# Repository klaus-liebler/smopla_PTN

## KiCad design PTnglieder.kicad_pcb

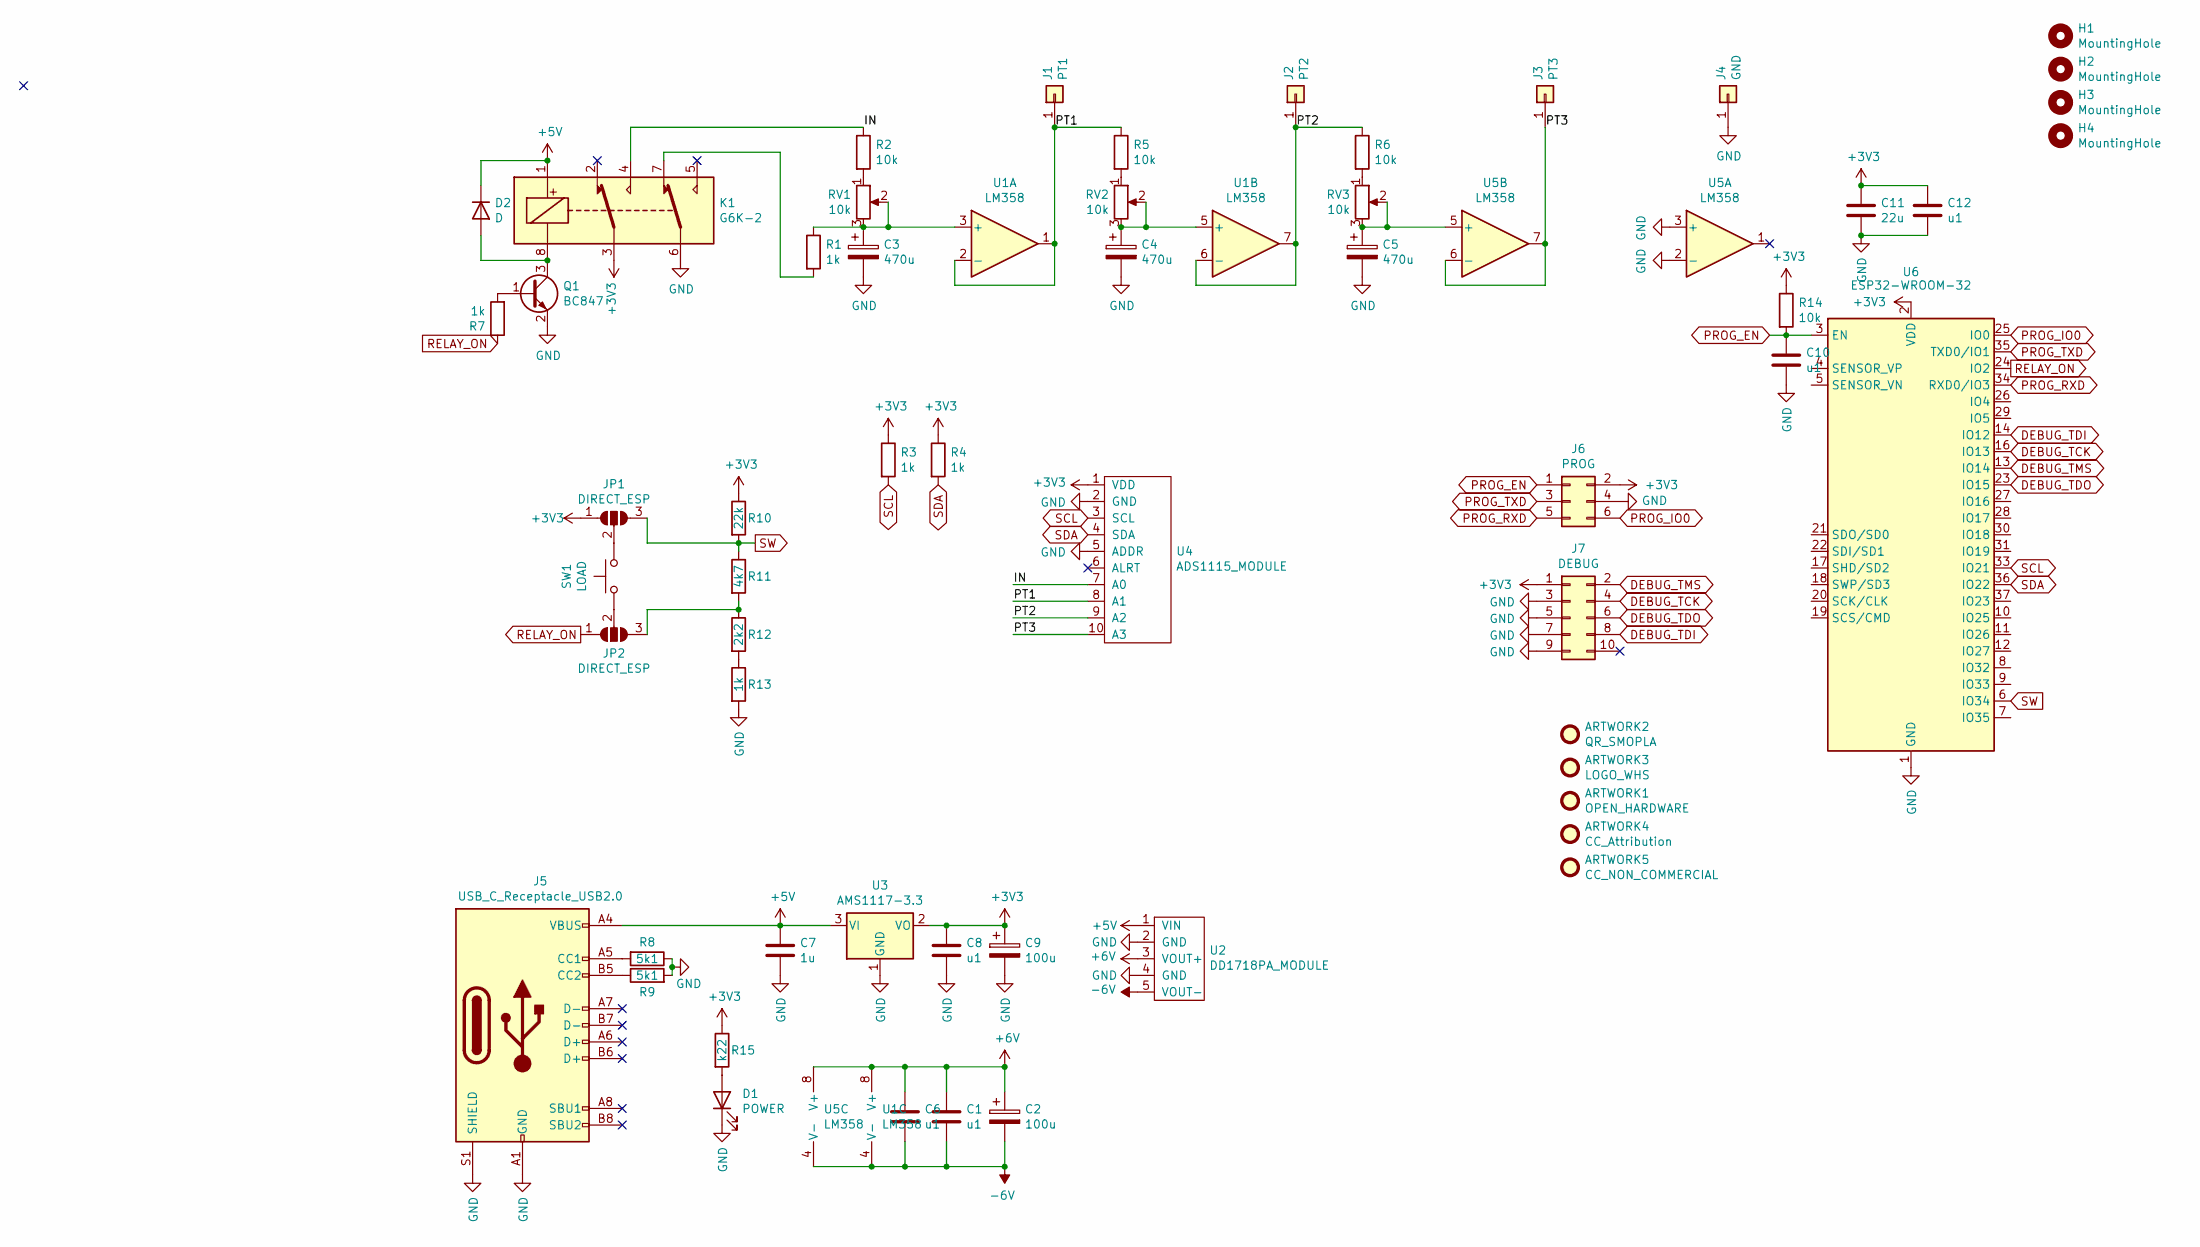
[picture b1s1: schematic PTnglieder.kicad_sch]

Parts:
ARTWORK1: OPEN_HARDWARE; OSHW-Logo2_14.6x12mm_Copper
ARTWORK2: QR_SMOPLA; QR_CODE_smopla_de
ARTWORK3: LOGO_WHS
ARTWORK4: CC_Attribution; Symbol_CC-Attribution_CopperTop_Big
ARTWORK5: CC_NON_COMMERCIAL; Symbol_CC-Noncommercial_CopperTop_Big
C1, C6, C8, C10, C12: u1; C_0805_2012Metric_Pad1.15x1.40mm_HandSolder
C2, C9: 100u; CP_Elec_6.3x5.7
C3, C4, C5: 470u; CP_Elec_10x10
C7: 1u; C_0805_2012Metric_Pad1.15x1.40mm_HandSolder
C11: 22u; C_1206_3216Metric_Pad1.42x1.75mm_HandSolder
D1: POWER; LED_D5.0mm
D2: D; D_SMA
H1, H2, H3, H4: MountingHole; MountingHole_3.2mm_M3_DIN965
J1: PT1; LABORATORY_JACK_RECESSED
J2: PT2; LABORATORY_JACK_RECESSED
J3: PT3; LABORATORY_JACK_RECESSED
J4: GND; LABORATORY_JACK_RECESSED
J5: USB_C_Receptacle_USB2.0; USB_C_Receptacle_HANDSOLDER
J6: PROG; PinHeader_2x03_P1.27mm_Vertical_SMD
J7: DEBUG; PinHeader_2x05_P1.27mm_Vertical_SMD
JP1, JP2: DIRECT_ESP; SolderJumper-3_P1.3mm_Open_RoundedPad1.0x1.5mm_NumberLabels
K1: G6K-2; Relay_DPDT_Omron_G6K-2F-Y_HANDSOLDER
Q1: BC847; SOT-23_Handsoldering
R1, R3, R4, R7, R13: 1k; R_0805_2012Metric_Pad1.15x1.40mm_HandSolder
R2, R5, R6, R14: 10k; R_0805_2012Metric_Pad1.15x1.40mm_HandSolder
R8, R9: 5k1; R_0805_2012Metric_Pad1.15x1.40mm_HandSolder
R10: 22k; R_0805_2012Metric_Pad1.15x1.40mm_HandSolder
R11: 4k7; R_0805_2012Metric_Pad1.15x1.40mm_HandSolder
R12: 2k2; R_0805_2012Metric_Pad1.15x1.40mm_HandSolder
R15: k22; R_0805_2012Metric_Pad1.15x1.40mm_HandSolder
RV1, RV2, RV3: 10k; Potentiometer_Alps_RK09K_Single_Vertical
SW1: LOAD; SW_PUSH-12mm_ANCHOR_CENTER
U1, U5: LM358; SOIC-8_3.9x4.9mm_Pitch1.27mm_handsolder
U2: DD1718PA_MODULE; DD1718PA_MODULE_SMD
U3: AMS1117-3.3; SOT-223-3_TabPin2_HANDSOLDER
U4: ADS1115_MODULE; ADS1115_MODULE_SMD
U6: ESP32-WROOM-32; ESP32-WROOM-32_HANDSOLDER

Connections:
+3V3: C8.1, C9.1, C11.1, C12.1, J6.2, J7.1, JP1.1 (A), K1.3, R3.1, R4.1, R10.1, R14.1, R15.1, U3.2 (VO), U4.1 (VDD), U6.2 (VDD)
+5V: C7.1, D2.1 (K), J5.A4 (VBUS), J5.A9 (VBUS), J5.B4 (VBUS), J5.B9 (VBUS), K1.1, U2.1 (VIN), U3.3 (VI)
+6V: C1.1, C2.1, C6.1, U1.8 (V+), U2.3 (VOUT+), U5.8 (V+)
-6V: C1.2, C2.2, C6.2, U1.4 (V-), U2.5 (VOUT-), U5.4 (V-)
/IN: K1.4, R2.1, U4.7 (A0)
/PT1: J1.1, R5.1, U1.1, U1.2 (-), U4.8 (A1)
/PT2: J2.1, R6.1, U1.6 (-), U1.7, U4.9 (A2)
/PT3: J3.1, U4.10 (A3), U5.6 (-), U5.7
DEBUG_TCK: J7.4, U6.16 (IO13)
DEBUG_TDI: J7.8, U6.14 (IO12)
DEBUG_TDO: J7.6, U6.23 (IO15)
DEBUG_TMS: J7.2, U6.13 (IO14)
GND: C3.2, C4.2, C5.2, C7.2, C8.2, C9.2, C10.2, C11.2, C12.2, D1.1 (K), J4.1, J5.A1 (GND), J5.A12 (GND), J5.B1 (GND), J5.B12 (GND), J5.S1 (SHIELD), J6.4, J7.3, J7.5, J7.7, J7.9, K1.6, Q1.2 (E), R8.1, R9.2, R13.2, U2.2 (GND), U2.4 (GND), U3.1 (GND), U4.2 (GND), U4.5 (ADDR), U5.2 (-), U5.3 (+), U6.1 (GND), U6.15 (GND), U6.38 (GND), U6.39 (GND)
unnamed: C3.1, R1.1, RV1.2, RV1.3, U1.3 (+)
unnamed: C4.1, RV2.2, RV2.3, U1.5 (+)
unnamed: C5.1, RV3.2, RV3.3, U5.5 (+)
unnamed: D1.2 (A), R15.2
unnamed: D2.2 (A), K1.8, Q1.3 (C)
unnamed: J5.A5 (CC1), R8.2
unnamed: J5.B5 (CC2), R9.1
unnamed: JP1.2 (C), SW1.2
unnamed: JP2.2 (C), SW1.1
unnamed: JP2.3 (B), R11.2, R12.1
unnamed: K1.7, R1.2
unnamed: Q1.1 (B), R7.2
unnamed: R2.2, RV1.1
unnamed: R5.2, RV2.1
unnamed: R6.2, RV3.1
unnamed: R12.2, R13.1
PROG_EN: C10.1, J6.1, R14.2, U6.3 (EN)
PROG_IO0: J6.6, U6.25 (IO0)
PROG_RXD: J6.5, U6.34 (RXD0/IO3)
PROG_TXD: J6.3, U6.35 (TXD0/IO1)
RELAY_ON: JP2.1 (A), R7.1, U6.24 (IO2)
SCL: R3.2, U4.3 (SCL), U6.33 (IO21)
SDA: R4.2, U4.4 (SDA), U6.36 (IO22)
SW: JP1.3 (B), R10.2, R11.1, U6.6 (IO34)

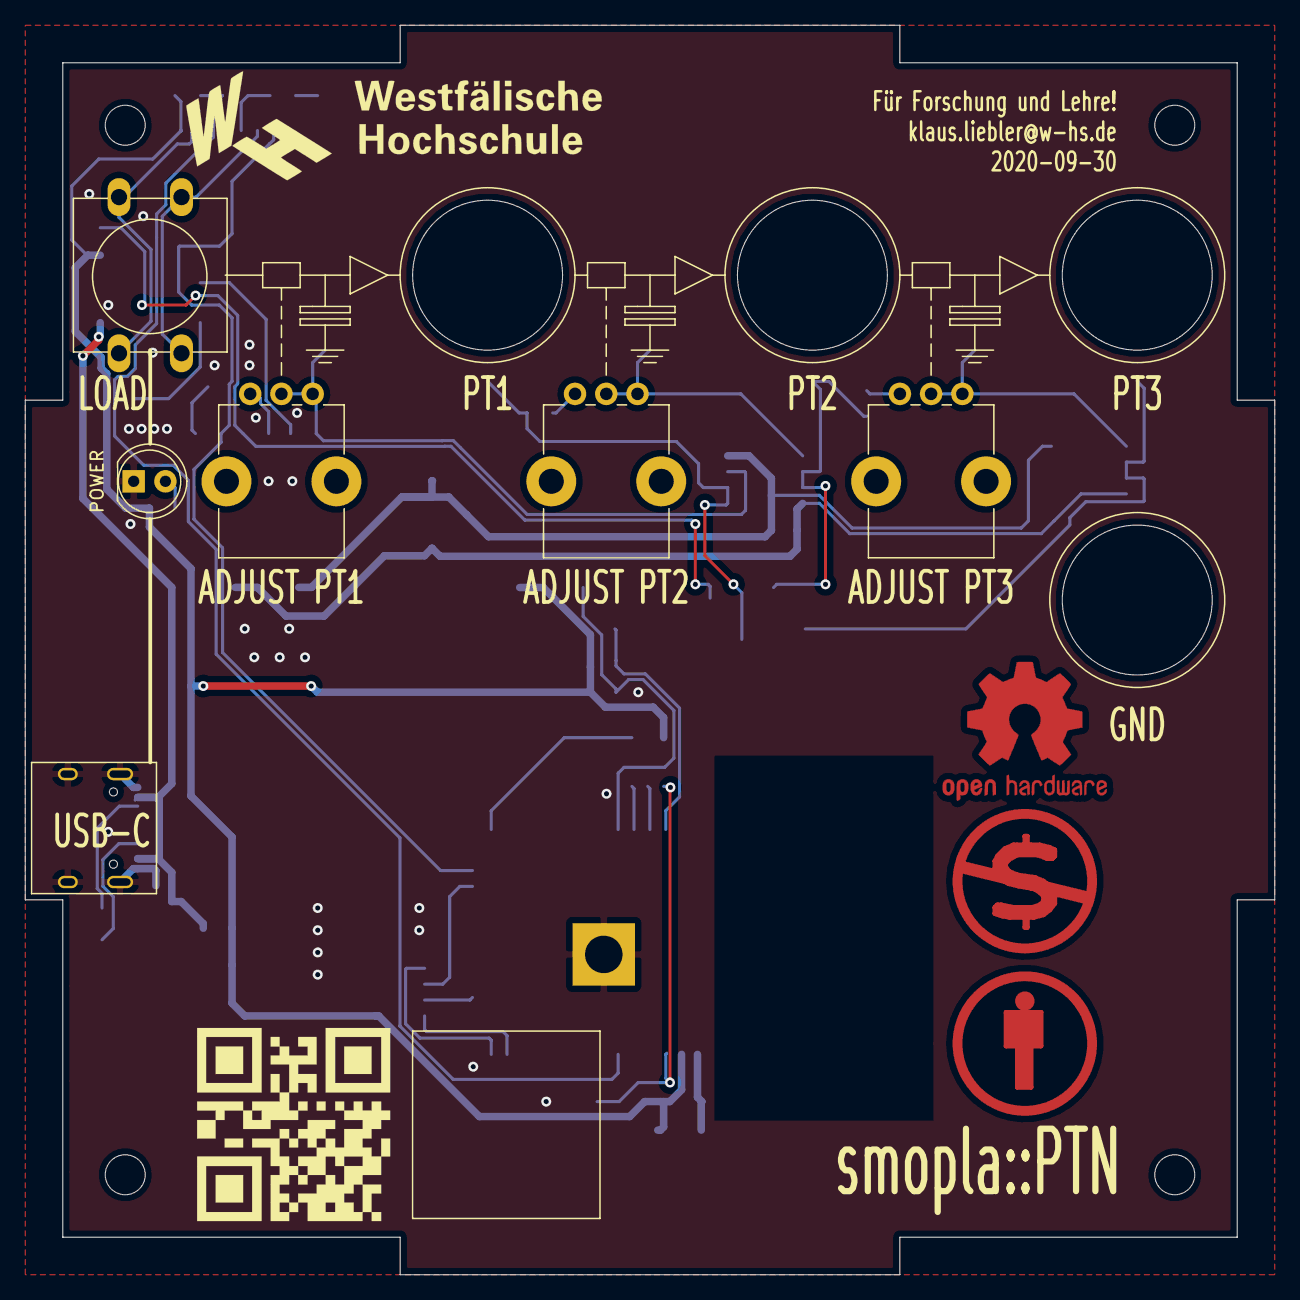
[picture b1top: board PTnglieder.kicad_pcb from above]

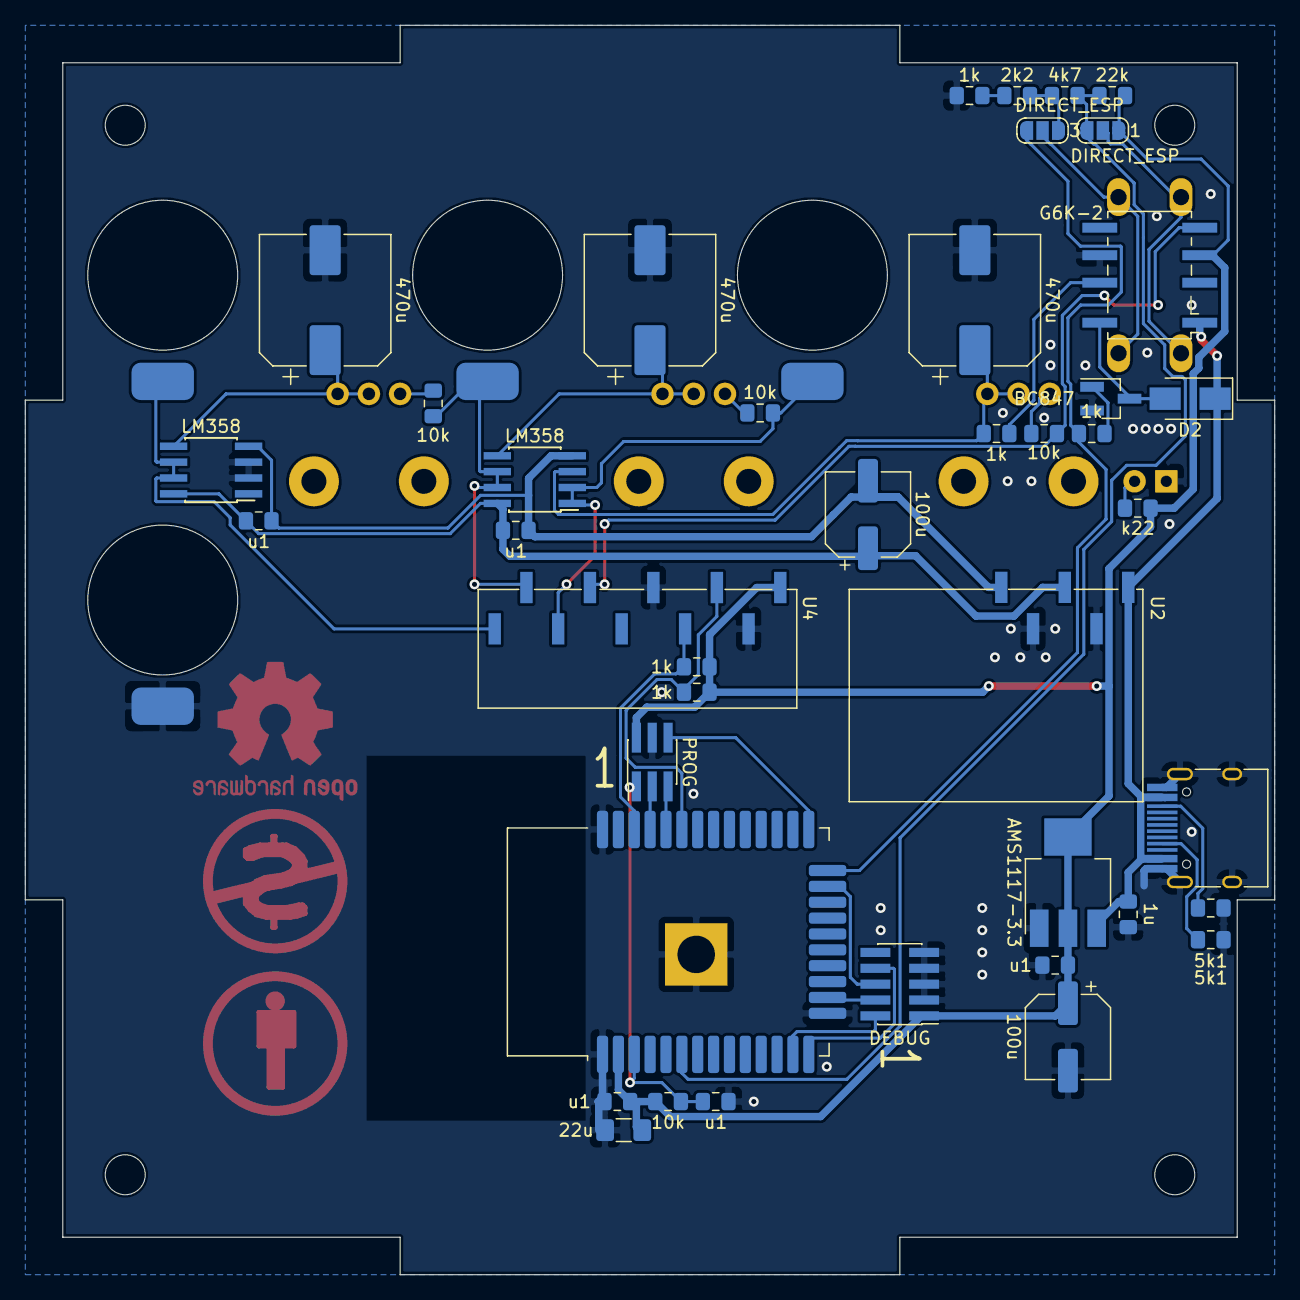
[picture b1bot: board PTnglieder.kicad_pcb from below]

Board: 2 copper layers, 100.0 x 100.0 mm, 59 parts (42 on the bottom side), 37 nets.

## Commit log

2020-11-14 Initial Version
2022-01-01 Update to new libs
2022-06-11 Various
